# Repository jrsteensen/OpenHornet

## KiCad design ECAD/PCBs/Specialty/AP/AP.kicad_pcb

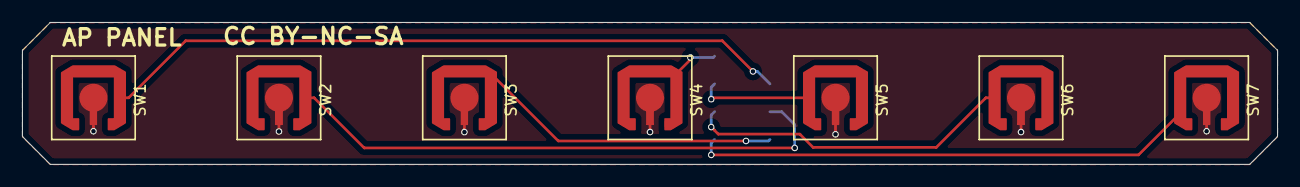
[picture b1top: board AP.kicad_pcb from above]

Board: 2 copper layers, 114.6 x 13.0 mm, 8 parts (1 on the bottom side), 8 nets.

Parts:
J1: Conn_02x04_Odd_Even; Pin_Header_Straight_2x04_Pitch2.54mm_SMD
SW1, SW2, SW3, SW4, SW5, SW6, SW7: SW_SPST; SWITCH_SNAP_DOME_6.3mm_DIA_SINGLE_SIDE_PCB

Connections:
unnamed: J1.1, SW1.1, SW2.1, SW3.1, SW4.1, SW5.1, SW6.1, SW7.1
unnamed: J1.2, SW4.2
unnamed: J1.3, SW1.2
unnamed: J1.4, SW5.2
unnamed: J1.5, SW2.2
unnamed: J1.6, SW6.2
unnamed: J1.7, SW3.2
unnamed: J1.8, SW7.2

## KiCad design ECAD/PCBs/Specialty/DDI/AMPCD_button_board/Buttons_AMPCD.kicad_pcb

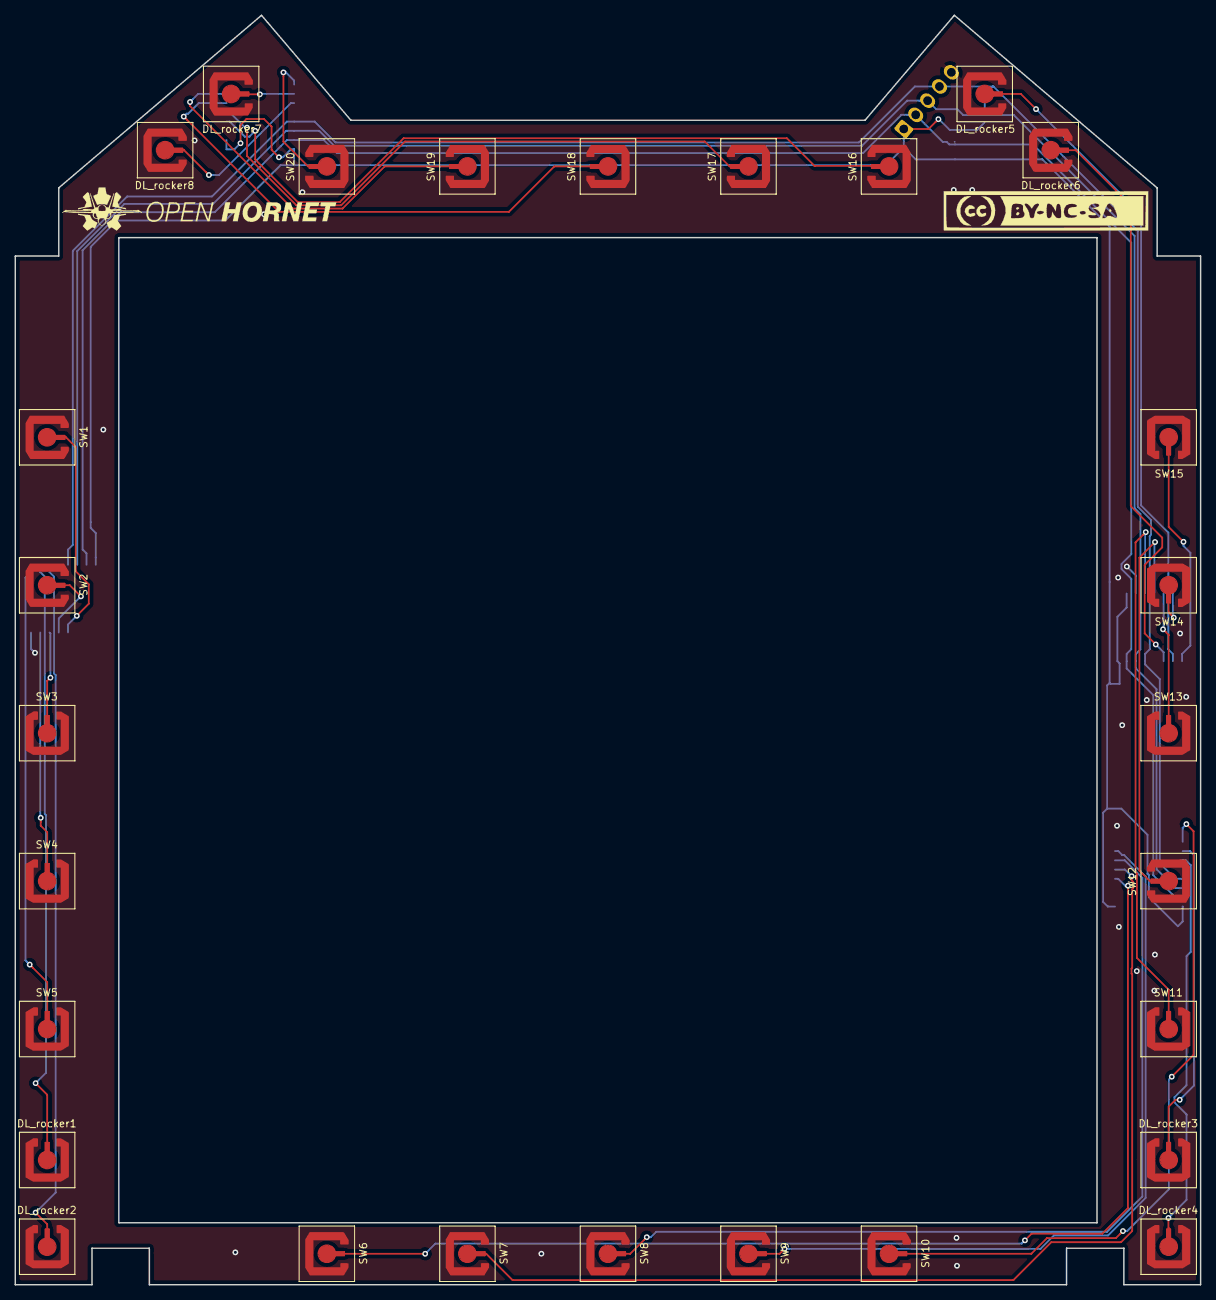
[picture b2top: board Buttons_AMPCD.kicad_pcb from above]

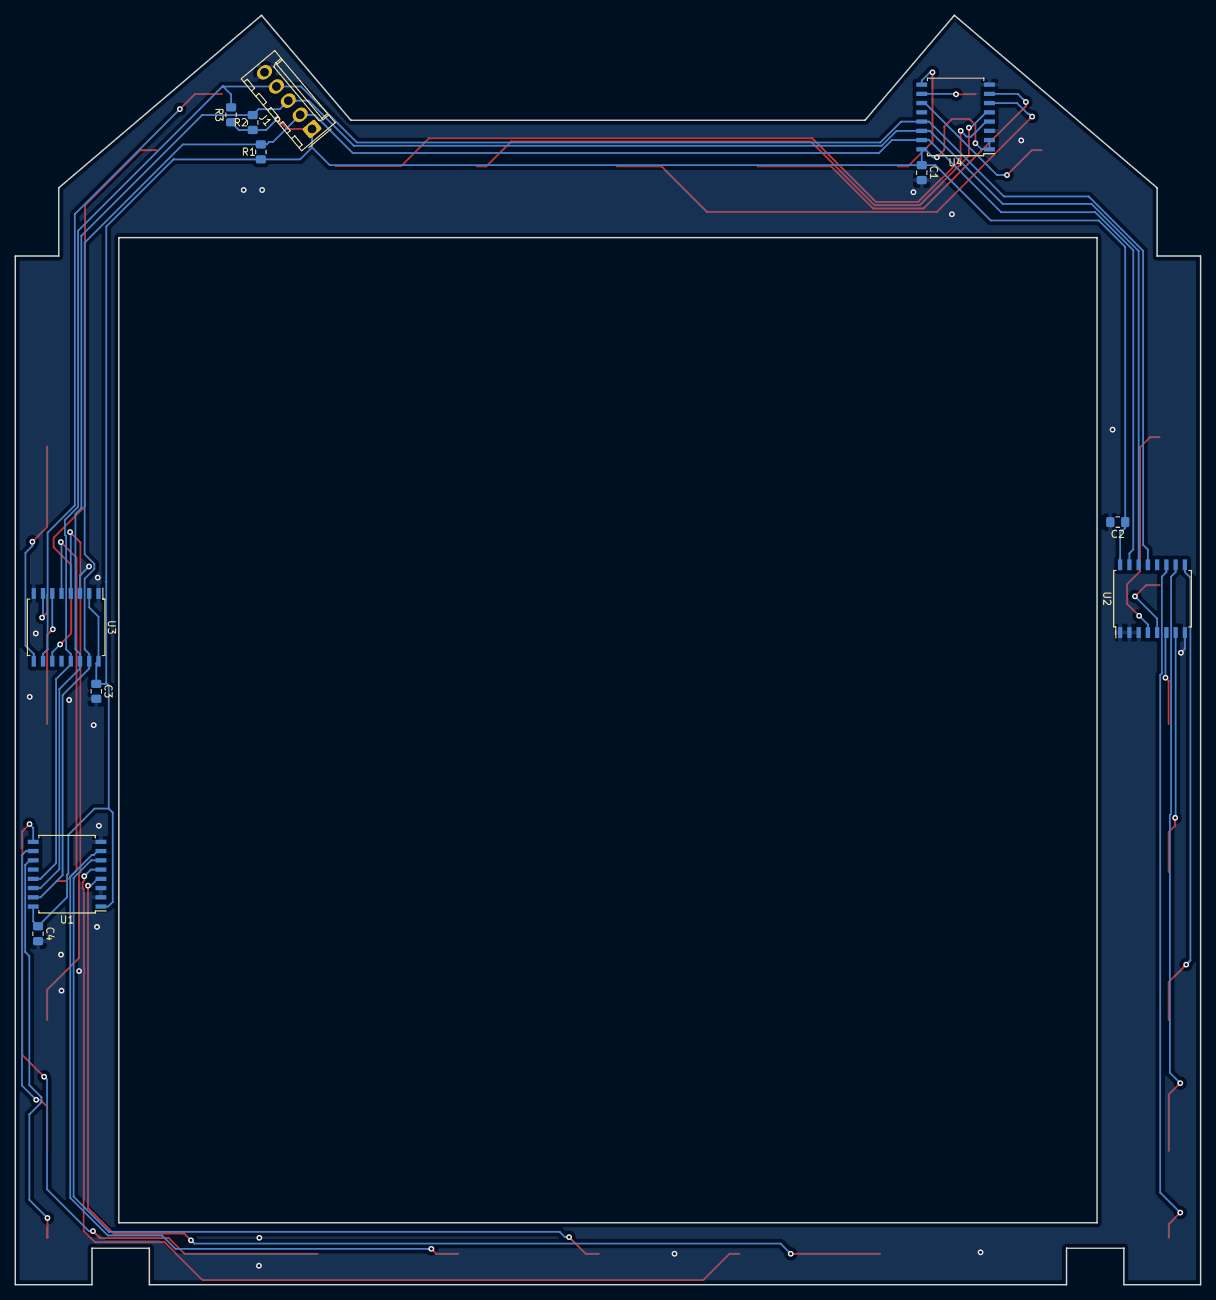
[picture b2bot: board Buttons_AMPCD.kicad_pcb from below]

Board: 2 copper layers, 162.8 x 174.4 mm, 40 parts (12 on the bottom side), 33 nets.

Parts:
C1, C2, C3, C4: 47uF; C_0805_2012Metric_Pad1.15x1.40mm_HandSolder
DL_rocker1, DL_rocker2, DL_rocker3, DL_rocker4, DL_rocker5, DL_rocker6, DL_rocker7, DL_rocker8: SW_Push; SWITCH_SNAP_DOME_6.3mm_DIA_SINGLE_SIDE_PCB
J1: ExpansionPort; Molex_KK-254_AE-6410-05A_1x05_P2.54mm_Vertical
R1, R2, R3: 1k; R_0805_2012Metric_Pad1.15x1.40mm_HandSolder
SW1, SW2, SW3, SW4, SW5, SW6, SW7, SW8, SW9, SW10, SW11, SW12, SW13, SW14, SW15, SW16, SW17, SW18, SW19, SW20: SW_Push; SWITCH_SNAP_DOME_6.3mm_DIA_SINGLE_SIDE_PCB
U1, U2, U3, U4: TCA9534; SOIC-16W_7.5x10.3mm_P1.27mm

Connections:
+5V: C1.1, C2.1, C3.1, C4.1, J1.1, R1.1, R2.1, R3.1, U1.1, U1.16, U2.16, U3.2, U3.16, U4.1, U4.2, U4.16
GND: C1.2, C2.2, C3.2, C4.2, DL_rocker1.2, DL_rocker2.2, DL_rocker3.2, DL_rocker4.2, DL_rocker5.2, DL_rocker6.2, DL_rocker7.2, DL_rocker8.2, J1.5, SW1.2, SW2.2, SW3.2, SW4.2, SW5.2, SW6.2, SW7.2, SW8.2, SW9.2, SW10.2, SW11.2, SW12.2, SW13.2, SW14.2, SW15.2, SW16.2, SW17.2, SW18.2, SW19.2, SW20.2, U1.2, U1.3, U1.8, U2.1, U2.2, U2.3, U2.8, U3.1, U3.3, U3.8, U4.3, U4.8
IRQ: J1.4, R3.2, U1.13, U2.13, U3.13, U4.13
unnamed: DL_rocker1.1, U2.10
unnamed: DL_rocker2.1, U2.11
unnamed: DL_rocker3.1, U1.10
unnamed: DL_rocker4.1, U1.11
unnamed: DL_rocker5.1, U3.10
unnamed: DL_rocker6.1, U3.11
unnamed: DL_rocker7.1, U4.10
unnamed: DL_rocker8.1, U4.11
unnamed: SW1.1, U2.4
unnamed: SW2.1, U2.5
unnamed: SW3.1, U2.6
unnamed: SW4.1, U2.7
unnamed: SW5.1, U2.9
unnamed: SW6.1, U1.4
unnamed: SW7.1, U1.5
unnamed: SW8.1, U1.6
unnamed: SW9.1, U1.7
unnamed: SW10.1, U1.9
unnamed: SW11.1, U3.4
unnamed: SW12.1, U3.5
unnamed: SW13.1, U3.6
unnamed: SW14.1, U3.7
unnamed: SW15.1, U3.9
unnamed: SW16.1, U4.4
unnamed: SW17.1, U4.5
unnamed: SW18.1, U4.6
unnamed: SW19.1, U4.7
unnamed: SW20.1, U4.9
SCL: J1.3, R2.2, U1.14, U2.14, U3.14, U4.14
SDA: J1.2, R1.2, U1.15, U2.15, U3.15, U4.15

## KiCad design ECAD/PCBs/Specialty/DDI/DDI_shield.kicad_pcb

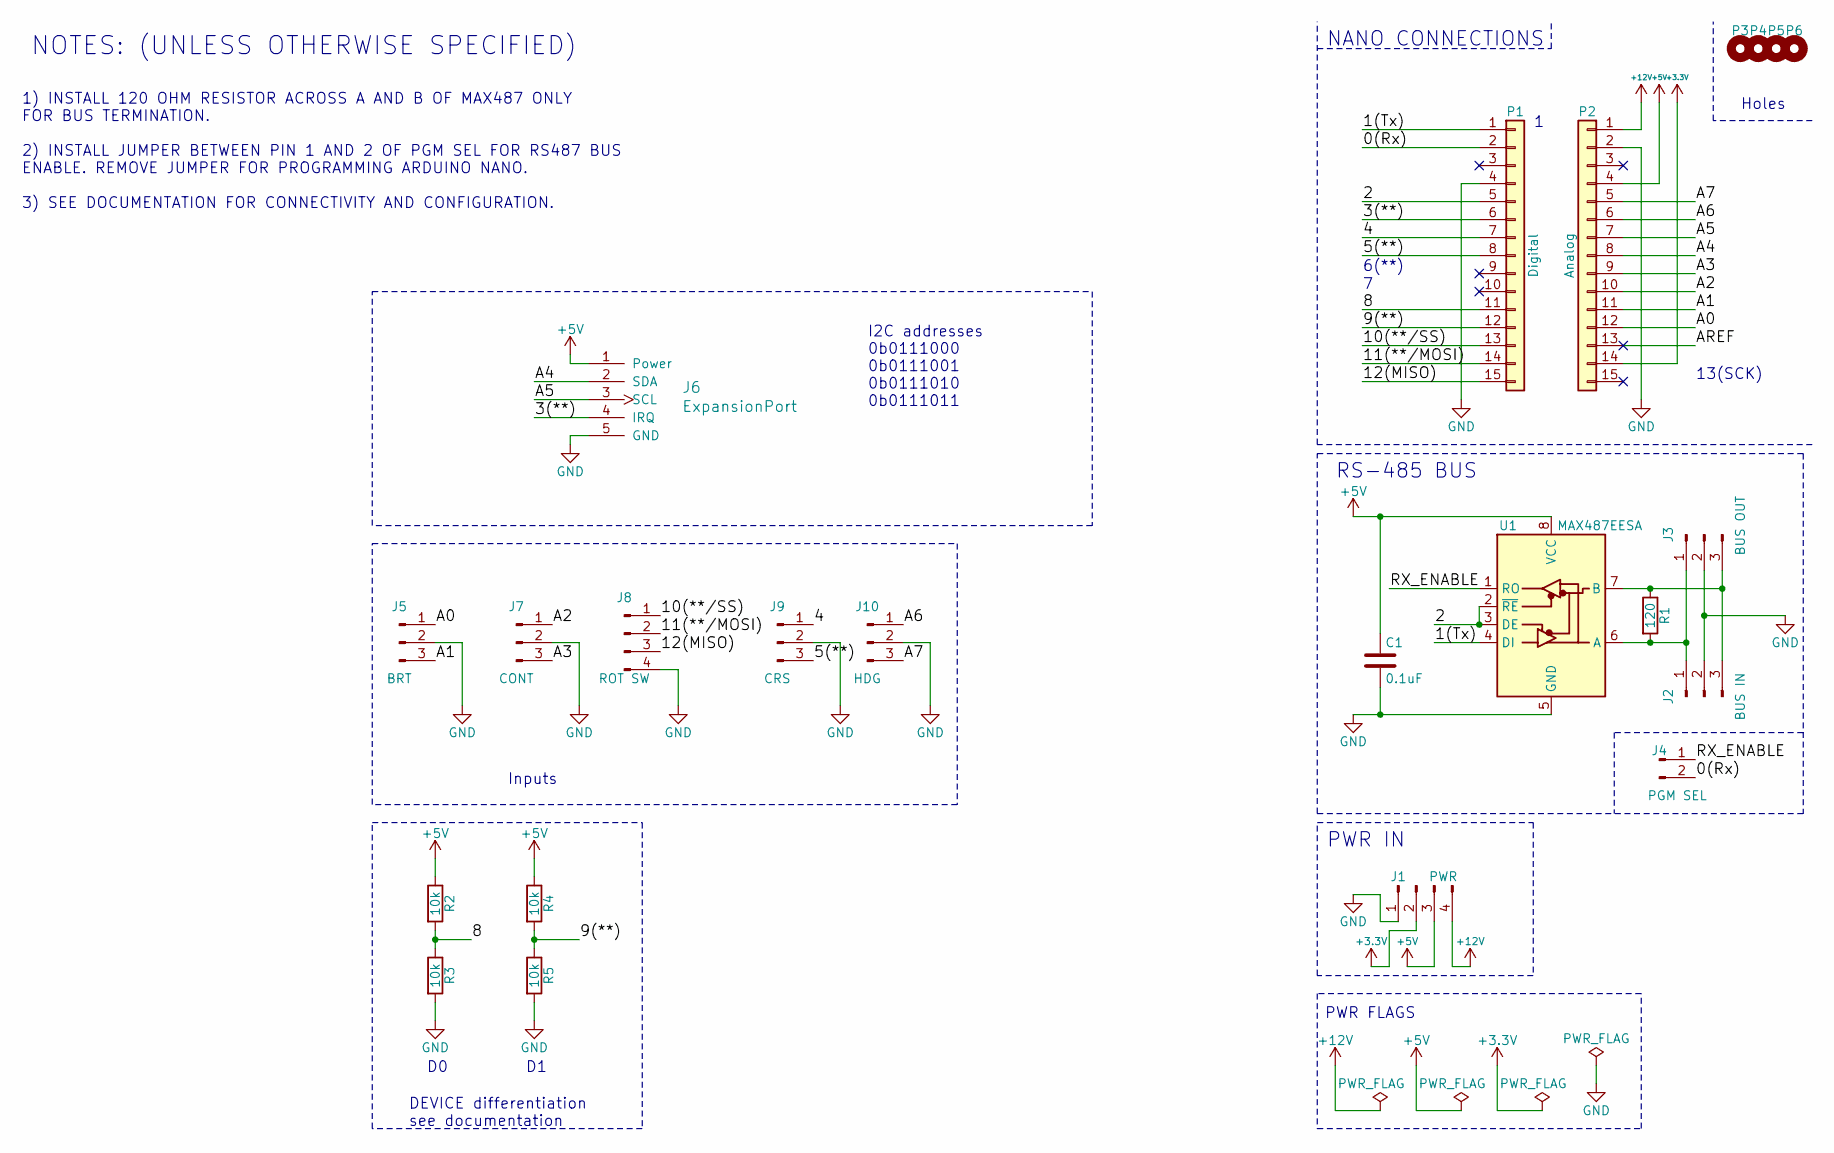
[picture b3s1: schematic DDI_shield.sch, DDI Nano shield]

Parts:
C1: 0.1uF; C_0805_2012Metric_Pad1.15x1.40mm_HandSolder
J1: PWR; Molex_KK-254_AE-6410-04A_1x04_P2.54mm_Vertical
J2: BUS IN; Molex_KK-254_AE-6410-03A_1x03_P2.54mm_Vertical
J3: BUS OUT; Molex_KK-254_AE-6410-03A_1x03_P2.54mm_Vertical
J4: PGM SEL; Pin_Header_Straight_1x02_Pitch2.54mm
J5: BRT; Molex_KK-254_AE-6410-03A_1x03_P2.54mm_Vertical
J6: ExpansionPort; PinHeader_1x05_P2.54mm_Vertical
J7: CONT; Molex_KK-254_AE-6410-03A_1x03_P2.54mm_Vertical
J8: ROT SW; PinHeader_1x04_P2.54mm_Vertical
J9: CRS; PinHeader_1x03_P2.54mm_Vertical
J10: HDG; PinHeader_1x03_P2.54mm_Vertical
P1: Digital; Socket_Strip_Arduino_1x15
P2: Analog; Socket_Strip_Arduino_1x15
P3, P4, P5, P6: mounting; 1pin_Nano
R1: 120; R_0805_2012Metric_Pad1.15x1.40mm_HandSolder
R2, R3, R4, R5: 10k; R_0805_2012Metric_Pad1.15x1.40mm_HandSolder
U1: MAX487EESA; SOIC-8_3.9x4.9mm_Pitch1.27mm

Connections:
+3V3: J1.2, P2.14
+5V: C1.1, J1.3, J6.1 (Power), P2.4, R2.1, R4.1, U1.8 (VCC)
+12V: J1.4, P2.1
/0(Rx): J4.2, P1.2
/1(Tx): P1.1, U1.4 (DI)
/2: P1.5, U1.2 (~RE), U1.3 (DE)
/3(**): J6.4 (IRQ), P1.6
/4: J9.1, P1.7
/5(**): J9.3, P1.8
/8: P1.11, R2.2, R3.1
/9(**): P1.12, R4.2, R5.1
/10(**/SS): J8.1, P1.13
/11(**/MOSI): J8.2, P1.14
/12(MISO): J8.3, P1.15
/A0: J5.1, P2.12
/A1: J5.3, P2.11
/A2: J7.1, P2.10
/A3: J7.3, P2.9
/A4: J6.2 (SDA), P2.8
/A5: J6.3 (SCL), P2.7
/A6: J10.1, P2.6
/A7: J10.3, P2.5
/AREF: P2.13
/RX_ENABLE: J4.1, U1.1 (RO)
GND: C1.2, J1.1, J2.2, J3.2, J5.2, J6.5 (GND), J7.2, J8.4, J9.2, J10.2, P1.4, P2.2, R3.2, R5.2, U1.5 (GND)
unnamed: J2.1, J3.1, R1.2, U1.6 (A)
unnamed: J2.3, J3.3, R1.1, U1.7 (B)

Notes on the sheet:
Holes
NANO CONNECTIONS
RS-485 BUS
1) INSTALL 120 OHM RESISTOR ACROSS A AND B OF MAX487 ONLY FOR BUS TERMINATION. 2) INSTALL JUMPER BETWEEN PIN 1 AND 2 OF PGM SEL FOR RS487 BUS ENABLE. REMOVE JUMPER FOR PROGRAMMING ARDUINO NANO. 3) SEE DOCUMENTATION FOR CONNECTIVITY AND CONFIGURATION.
NOTES: (UNLESS OTHERWISE SPECIFIED)
PWR IN
PWR FLAGS
Inputs
I2C addresses 0b0111000 0b0111001 0b0111010 0b0111011
DEVICE differentiation see documentation
13(SCK)
6(**)

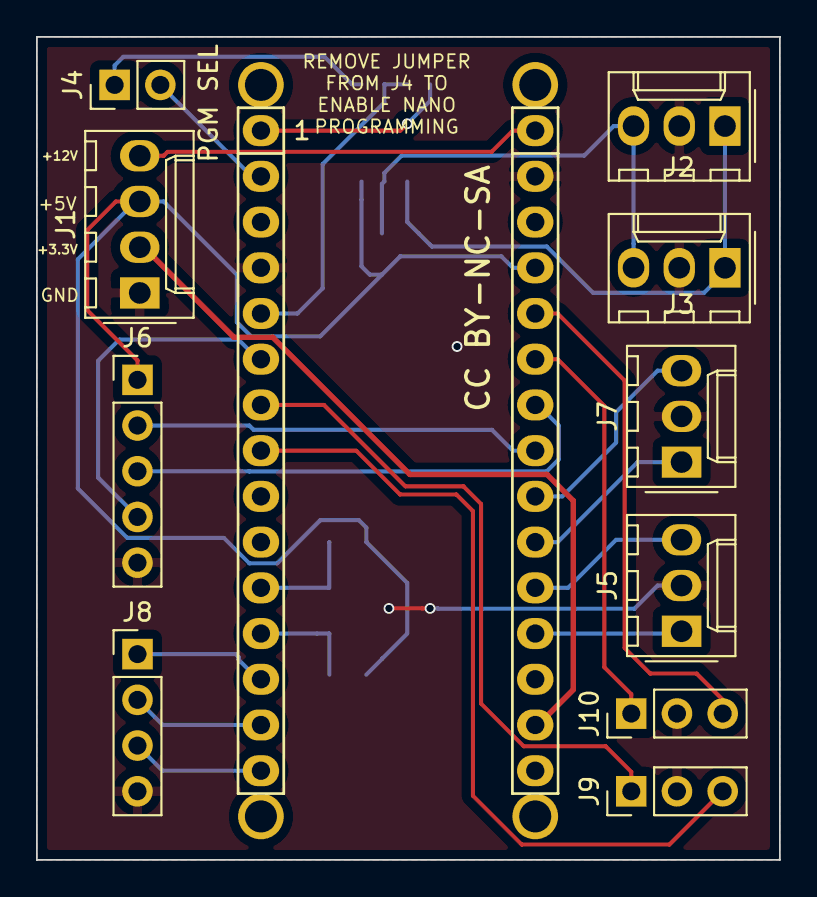
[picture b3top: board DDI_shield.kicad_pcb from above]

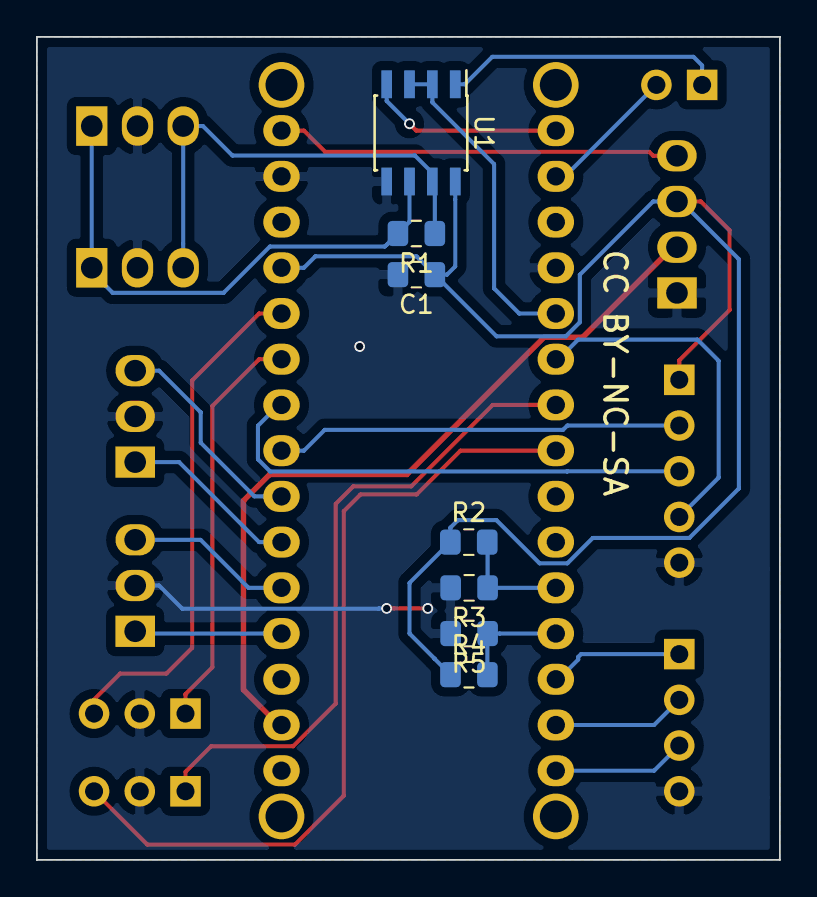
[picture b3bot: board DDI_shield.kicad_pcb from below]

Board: 2 copper layers, 41.3 x 45.7 mm, 23 parts (7 on the bottom side), 26 nets.

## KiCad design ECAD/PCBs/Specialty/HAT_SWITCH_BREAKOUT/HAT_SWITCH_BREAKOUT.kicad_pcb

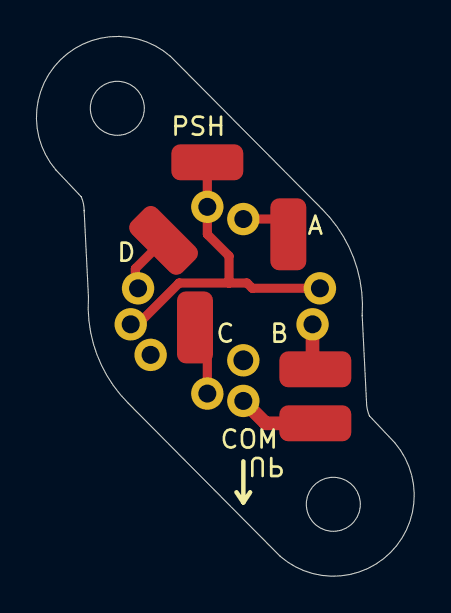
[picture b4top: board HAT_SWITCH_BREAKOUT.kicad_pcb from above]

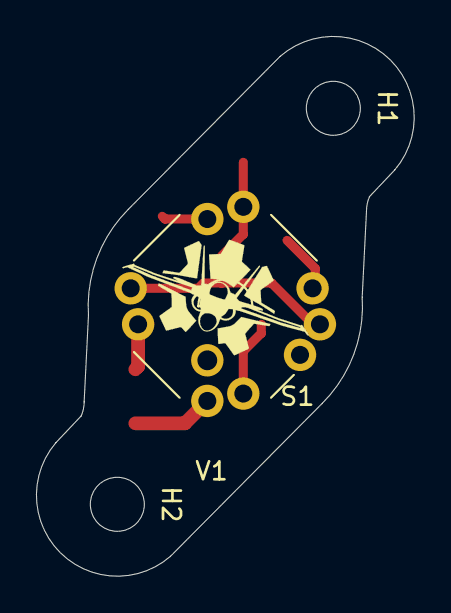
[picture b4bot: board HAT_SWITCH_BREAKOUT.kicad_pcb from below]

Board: 2 copper layers, 21.0 x 30.0 mm, 9 parts (3 on the bottom side), 6 nets.

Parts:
H1, H2: MountingHole; MountingHole_3mm
J1, J2, J3, J4, J5, J6: Conn_01x01; SolderWirePad_1x01_SMD_2x4mm
S1: 8WayHat_CenterPush; RKJXM10

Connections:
unnamed: J1.1, S1.A
unnamed: J2.1, S1.B
unnamed: J3.1, S1.C
unnamed: J4.1, S1.D
unnamed: J5.1, S1.PUSH1, S1.PUSH2, S1.PUSH3
unnamed: J6.1, S1.COM

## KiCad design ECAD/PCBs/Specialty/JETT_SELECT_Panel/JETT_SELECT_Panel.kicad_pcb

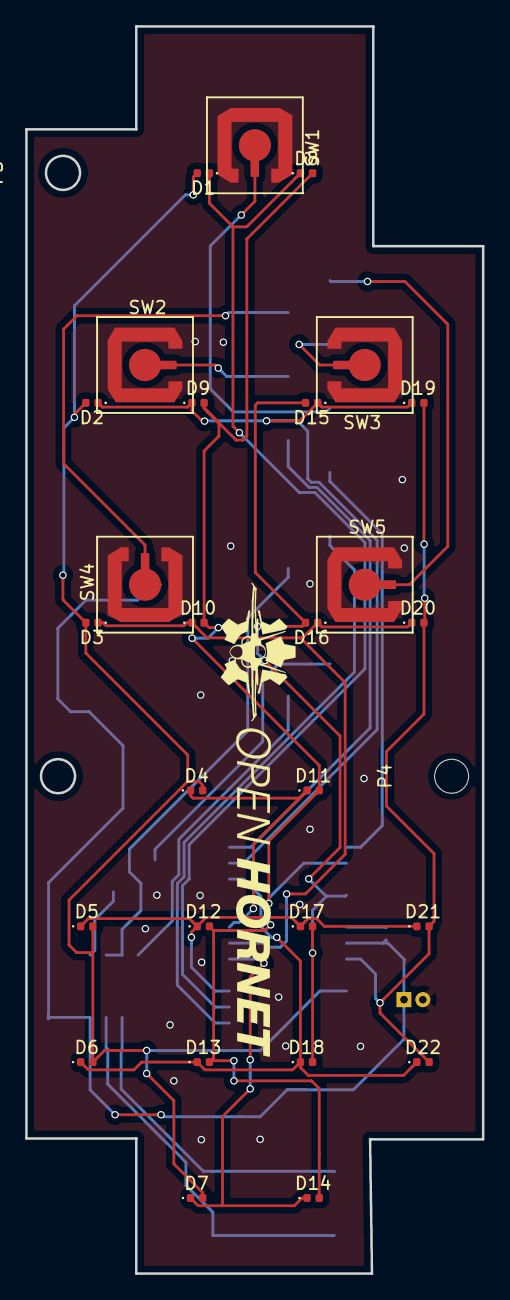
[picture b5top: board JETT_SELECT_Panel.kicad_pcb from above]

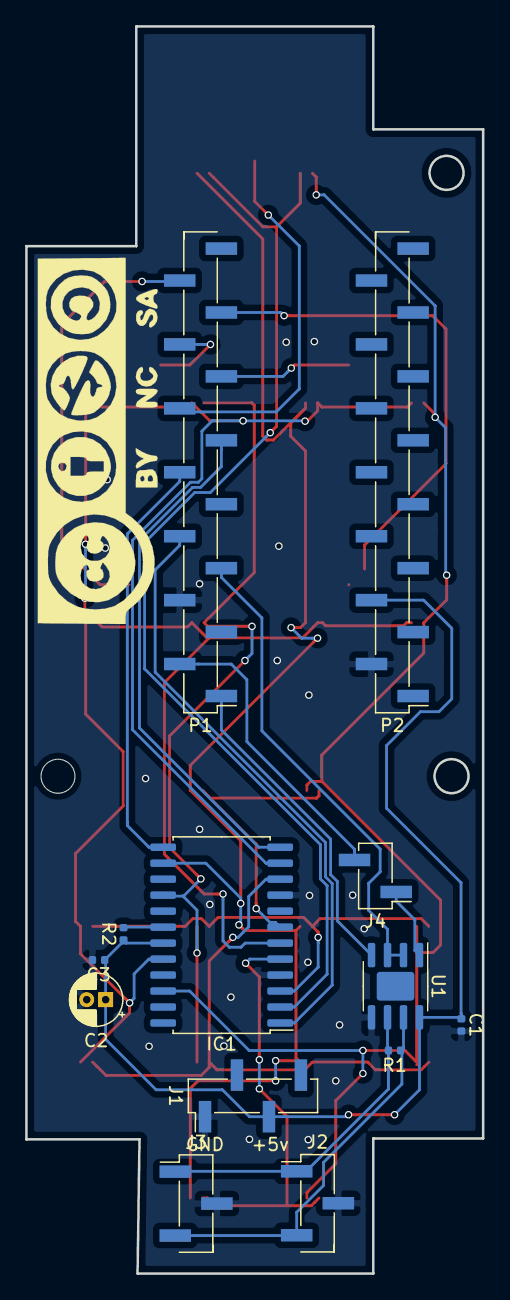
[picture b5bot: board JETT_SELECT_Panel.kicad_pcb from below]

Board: 2 copper layers, 36.3 x 99.1 mm, 43 parts (13 on the bottom side), 28 nets.

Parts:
C1: 0.1uF; C_0402_1005Metric
C2: 47uF; CP_Radial_D4.0mm_P1.50mm
C3: 100nF; C_0402_1005Metric
D1: 0,0; LED_0402_1005Metric
D2: 1,0; LED_0402_1005Metric
D3: 2,0; LED_0402_1005Metric
D4: 3,0; LED_0402_1005Metric
D5: 4,0; LED_0402_1005Metric
D6: 5,0; LED_0402_1005Metric
D7: 6,0; LED_0402_1005Metric
D8: 0,1; LED_0402_1005Metric
D9: 1,1; LED_0402_1005Metric
D10: 2,1; LED_0402_1005Metric
D11: 3,1; LED_0402_1005Metric
D12: 4,1; LED_0402_1005Metric
D13: 5,1; LED_0402_1005Metric
D14: 6,1; LED_0402_1005Metric
D15: 1,2; LED_0402_1005Metric
D16: 2,2; LED_0402_1005Metric
D17: 4,2; LED_0402_1005Metric
D18: 5,2; LED_0402_1005Metric
D19: 1,3; LED_0402_1005Metric
D20: 2,3; LED_0402_1005Metric
D21: 4,3; LED_0402_1005Metric
D22: 5,3; LED_0402_1005Metric
IC1: MAX7219; SOIC-24W_7.5x15.4mm_P1.27mm
J1: PWR; PinHeader_1x04_P2.54mm_Vertical_SMD_Pin1Left
J2: BUS IN; PinHeader_1x03_P2.54mm_Vertical_SMD_Pin1Left
J3: BUS OUT; PinHeader_1x03_P2.54mm_Vertical_SMD_Pin1Left
J4: PGM ENBLE; PinHeader_1x02_P2.54mm_Vertical_SMD_Pin1Left
P1: Digital; PinHeader_1x15_P2.54mm_Vertical_SMD_Pin1Left
P2: Analog; PinHeader_1x15_P2.54mm_Vertical_SMD_Pin1Left
P3, P4, P5: CONN_01X01; MountingHole_2.7mm_M2.5
R1: 120; R_0402_1005Metric
R2: 30K; R_0402_1005Metric
SW1, SW2, SW3, SW4, SW5: SW_Push; SWITCH_SNAP_DOME_6.3mm_DIA_SINGLE_SIDE_PCB
U1: MAX487EESA+T; SOIC-8-1EP_3.9x4.9mm_P1.27mm_EP2.29x3mm

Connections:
+5V: C1.1, C2.1, C3.1, IC1.19, J1.3, P2.4, R2.1, U1.8
/0(Rx): J4.2, P1.2
/1(Tx): P1.1, U1.4
/2: P1.5, U1.2, U1.3
/3(**): IC1.1, P1.6
/5(**): IC1.13, P1.8
/6(**): IC1.12, P1.9
/7: P1.10, SW1.1
/8: P1.11, SW2.1
/9(**): P1.12, SW3.1
/10(**/SS): P1.13, SW4.1
/11(**/MOSI): P1.14, SW5.1
/Dig0: D1.1, D8.1, IC1.2
/Dig1: D2.1, D9.1, D15.1, D19.1, IC1.11
/Dig2: D3.1, D10.1, D16.1, D20.1, IC1.6
/Dig3: D4.1, D11.1, IC1.7
/Dig4: D5.1, D12.1, D17.1, D21.1, IC1.3
/Dig5: D6.1, D13.1, D18.1, D22.1, IC1.10
/Dig6: D7.1, D14.1, IC1.5
/RX_ENABLE: J4.1, U1.1
/SegA: D8.2, D9.2, D10.2, D11.2, D12.2, D13.2, D14.2, IC1.14
/SegB: D15.2, D16.2, D17.2, D18.2, IC1.16
/SegC: D19.2, D20.2, D21.2, D22.2, IC1.20
/SegDP: D1.2, D2.2, D3.2, D4.2, D5.2, D6.2, D7.2, IC1.22
GND: C1.2, C2.2, C3.2, IC1.4, IC1.9, J1.1, J2.2, J3.2, P1.4, P2.2, SW1.2, SW2.2, SW3.2, SW4.2, SW5.2, U1.5
unnamed: IC1.18, R2.2
unnamed: J2.1, J3.1, R1.2, U1.6
unnamed: J2.3, J3.3, R1.1, U1.7

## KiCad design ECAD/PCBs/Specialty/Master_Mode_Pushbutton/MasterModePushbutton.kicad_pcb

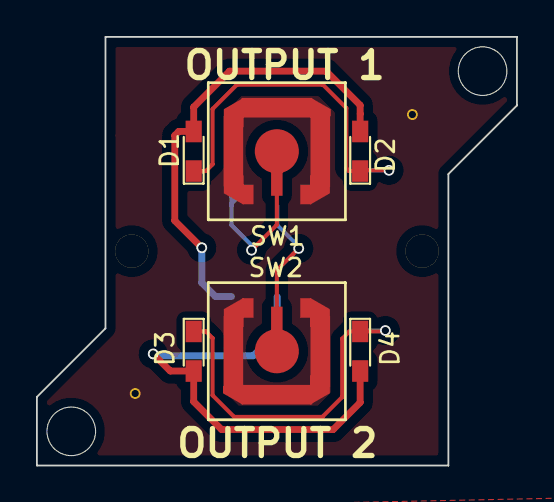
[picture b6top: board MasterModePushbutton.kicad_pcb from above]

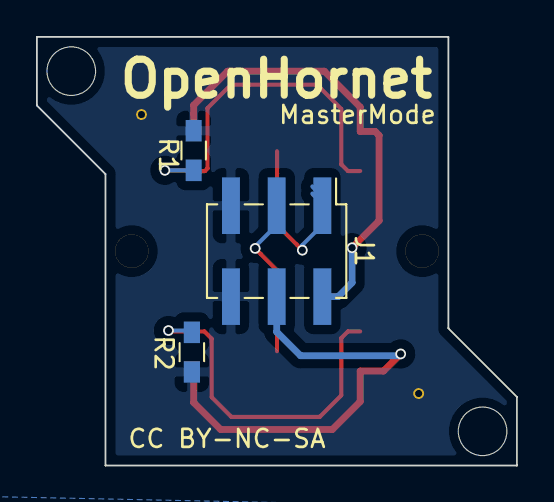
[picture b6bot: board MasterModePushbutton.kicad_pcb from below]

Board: 2 copper layers, 26.7 x 23.8 mm, 9 parts (3 on the bottom side), 7 nets.

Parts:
D1, D2, D3, D4: LED; LED_0603_HandSoldering
J1: Conn_02x03; Pin_Header_Straight_2x03_Pitch2.54mm_SMD
R1, R2: 68; R_0603_HandSoldering
SW1, SW2: push; SWITCH_SNAP_DOME_6.3mm_DIA_SINGLE_SIDE_PCB

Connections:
/backlight_1: D1.2, D2.2, J1.2
/backlight_2: D3.2, D4.2, J1.4
/switch1: J1.1, SW1.1
/switch2: J1.3, SW2.1
GND: J1.5, J1.6, R1.1, R2.1, SW1.2, SW2.2
unnamed: D1.1, D2.1, R1.2
unnamed: D3.1, D4.1, R2.2

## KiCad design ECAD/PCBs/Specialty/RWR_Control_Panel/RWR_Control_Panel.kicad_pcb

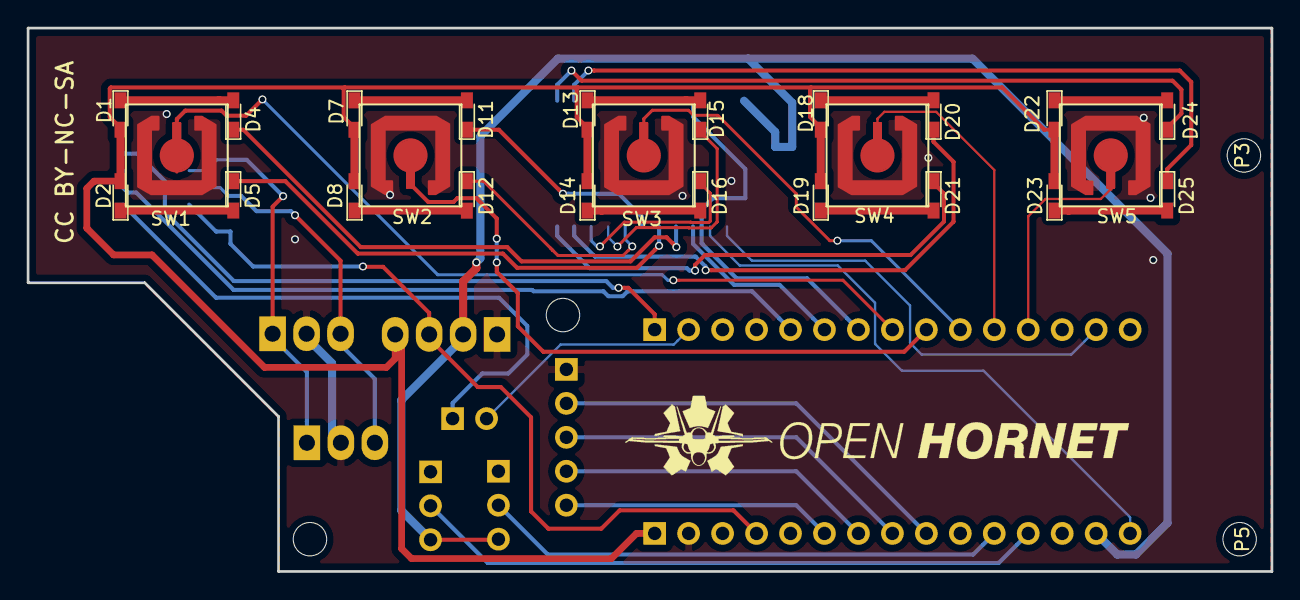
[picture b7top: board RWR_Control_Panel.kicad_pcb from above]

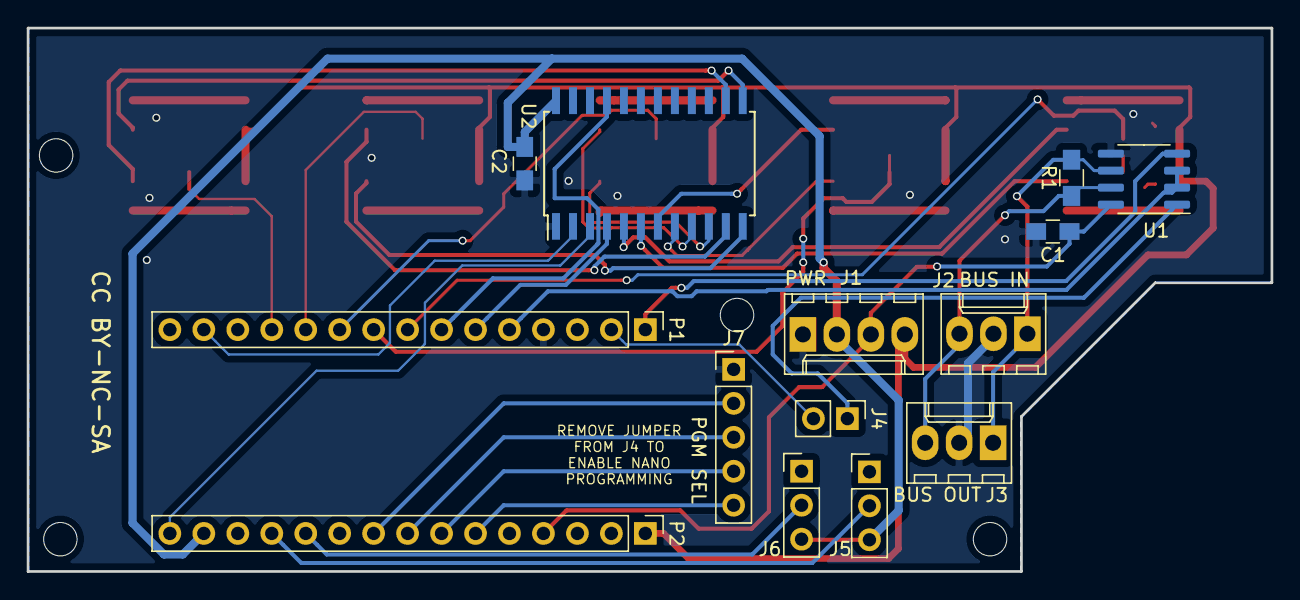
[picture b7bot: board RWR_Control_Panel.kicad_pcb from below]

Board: 2 copper layers, 93.0 x 40.6 mm, 43 parts (14 on the bottom side), 45 nets.

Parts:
C1: 0.1uF; C_0805_HandSoldering
C2: 100nF; C_0805_HandSoldering
D1, D2, D4, D5, D7, D8, D11, D12, D13, D14, D15, D16, D18, D19, D20, D21, D22, D23, D24, D25: WHT; LED_0603_HandSoldering
J1: PWR; Molex_KK-6410-04_04x2.54mm_Straight
J2: BUS IN; Molex_KK-6410-03_03x2.54mm_Straight
J3: BUS OUT; Molex_KK-6410-03_03x2.54mm_Straight
J4: PGM SEL; Pin_Header_Straight_1x02_Pitch2.54mm
J5: RPOT1; Pin_Header_Straight_1x03_Pitch2.54mm
J6: RPOT2; Pin_Header_Straight_1x03_Pitch2.54mm
J7: 5POS; Pin_Header_Straight_1x05_Pitch2.54mm
P1: Digital; Socket_Strip_Straight_1x15_Pitch2.54mm
P2: Analog; Socket_Strip_Straight_1x15_Pitch2.54mm
P3, P4, P5, P6: CONN_01X01; MountingHole_2.5mm
R1: 120; R_0805_HandSoldering
SW1, SW2, SW3, SW4, SW5: SW_Push; SWITCH_SNAP_DOME_6.3mm_DIA_SINGLE_SIDE_PCB
U1: MAX487EESA; SOIC-8_3.9x4.9mm_P1.27mm
U2: STP16CPC26; SOIC-24W_7.5x15.4mm_Pitch1.27mm

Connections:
+3V3: C2.1, J1.2, J5.3, J6.3, P2.14, U2.24
+5V: C1.1, J1.3, P2.4, U1.8
+12V: D1.2, D2.2, D7.2, D8.2, D13.2, D14.2, D18.2, D19.2, D22.2, D23.2, J1.4, P2.1
/0(Rx): J4.2, P1.2
/1(Tx): P1.1, U1.4
/2: P1.5, U1.2, U1.3
/3(**): P1.6, U2.4
/4: P1.7, U2.21
/5(**): P1.8, SW1.1
/6(**): P1.9, SW2.1
/7: P1.10, SW3.1
/8: P1.11, SW4.1
/9(**): P1.12, SW5.1
/11(**/MOSI): P1.14, U2.2
/13(SCK): P2.15, U2.3
/A0: J5.2, P2.12
/A1: J6.2, P2.11
/A3: J7.2, P2.9
/A4: J7.3, P2.8
/A5: J7.4, P2.7
/A6: J7.5, P2.6
/RX_ENABLE: J4.1, U1.1
GND: C1.2, C2.2, J1.1, J2.2, J3.2, J7.1, P1.4, P2.2, SW1.2, SW2.2, SW3.2, SW4.2, SW5.2, U1.5, U2.1
unnamed: D1.1, D4.2
unnamed: D2.1, D5.2
unnamed: D4.1, U2.5
unnamed: D5.1, U2.6
unnamed: D11.1, U2.7
unnamed: D7.1, D11.2
unnamed: D12.1, U2.8
unnamed: D8.1, D12.2
unnamed: D13.1, D15.2
unnamed: D14.1, D16.2
unnamed: D15.1, U2.9
unnamed: D16.1, U2.10
unnamed: D18.1, D20.2
unnamed: D19.1, D21.2
unnamed: D20.1, U2.11
unnamed: D21.1, U2.12
unnamed: D22.1, D24.2
unnamed: D23.1, D25.2
unnamed: D24.1, U2.13
unnamed: D25.1, U2.14
unnamed: J2.1, J3.1, R1.2, U1.6
unnamed: J2.3, J3.3, R1.1, U1.7

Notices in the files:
ECAD/PCBs/Specialty/AP/AP.kicad_pcb:
CC BY-NC-SA
